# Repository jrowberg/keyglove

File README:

==What is Keyglove?

The Keyglove is an [http://arduino.cc Arduino]-powered glove that uses touch combinations to generate keyboard and mouse control codes. Once learned, the glove can easily be used without looking, making it perfect for embedded/wearable environments. The glove is thin and light, built to allow other activities (such as writing or driving) without being in the way.

==Keyglove Design

Because the glove design allows for multi-sensor combinations, the keyglove provides exponentially more possibilities than many other glove-based input devices (prototypes or commercial products). 34 strategically placed contact sensors and smart controller software make it possible to implement the entire English alphabet using simple one-to-one sensor contacts. When you include multi-sensor contacts, there are many hundreds of ergonomically usable combinations.

==Development Status

As of October 2010, the glove is currently in the prototype stage with no fully working unit, but I've done a lot of development and testing on it. At the moment, I'm only waiting on a little more hardware to arrive in the mail before I should be able to complete a working model. The source code is logically sound and works as much as possible without the remaining hardware to test it.

For up-to-date development news, check out the [http://keyglove.net/news News] page ([http://keyglove.net/feed RSS here]) or follow the project on Twitter at [http://twitter.com/keyglove @keyglove].

For technical information, please visit the [http://keyglove.net/hardware Hardware] and [http://keyglove.net/software Software] pages. Once the prototype is working, I will add step-by-step instructions to the [http://keyglove.net/build Build Your Own] page (which is currently devoid of any decent content except a [http://keyglove.net/build rather entertaining photo]).

You may also be interested in a [http://keyglove.net/similar list of similar devices] I've come across on the internet recently, either to satisfy your curiosity, or out of a need for inspiration, or possibly to look for a product that might be more suited to your needs.

And, of course, you can always [http://keyglove.net/contact contact me] with any questions, comments, ideas, etc.

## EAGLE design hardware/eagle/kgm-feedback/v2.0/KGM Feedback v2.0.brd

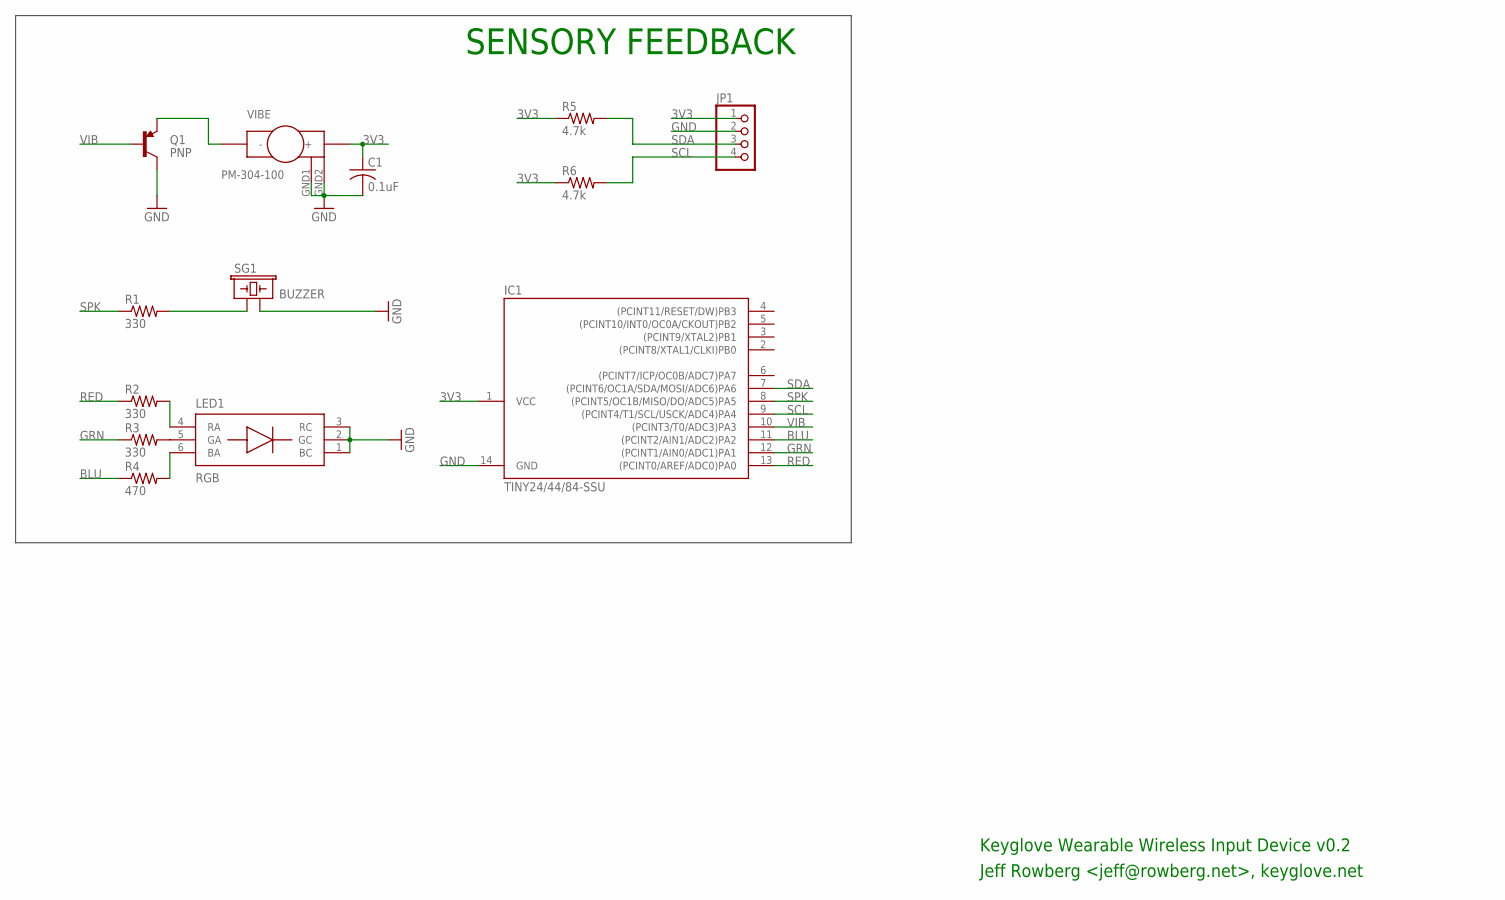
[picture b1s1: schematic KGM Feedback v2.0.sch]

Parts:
C1: 0.1uF; C0603
IC1: TINY24/44/84-SSU; SOIC14
JP1: PINHD-1X4; 1X04
LED1: RGB; PLCC-6
Q1: PNP; SOT23-3
R1, R2, R3: 330; R0603
R4: 470; R0603
R5, R6: 4.7k; R0603
SG1: BUZZER; BUZZER-CMT1102
VIBE: PM-304-100

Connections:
3V3: C1.1, IC1.1 (VCC), JP1.1, R5.1, R6.1, VIBE.+
BLU: IC1.11 ((PCINT2/AIN1/ADC2)PA2), R4.1
GND: C1.2, IC1.14 (GND), JP1.2, LED1.1 (BC), LED1.2 (GC), LED1.3 (RC), Q1.3 (C), SG1.2, VIBE.GND1 (GND), VIBE.GND2 (GND)
GRN: IC1.12 ((PCINT1/AIN0/ADC1)PA1), R3.1
unnamed: R1.2, SG1.1
unnamed: LED1.5 (GA), R3.2
unnamed: LED1.4 (RA), R2.2
unnamed: LED1.6 (BA), R4.2
unnamed: Q1.2 (E), VIBE.-
RED: IC1.13 ((PCINT0/AREF/ADC0)PA0), R2.1
SCL: IC1.9 ((PCINT4/T1/SCL/USCK/ADC4)PA4), JP1.4, R6.2
SDA: IC1.7 ((PCINT6/OC1A/SDA/MOSI/ADC6)PA6), JP1.3, R5.2
SPK: IC1.8 ((PCINT5/OC1B/MISO/DO/ADC5)PA5), R1.1
VIB: IC1.10 ((PCINT3/T0/ADC3)PA3), Q1.1 (B)

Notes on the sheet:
SENSORY FEEDBACK
Keyglove Wearable Wireless Input Device v0.2
Jeff Rowberg <jeff@rowberg.net>, keyglove.net

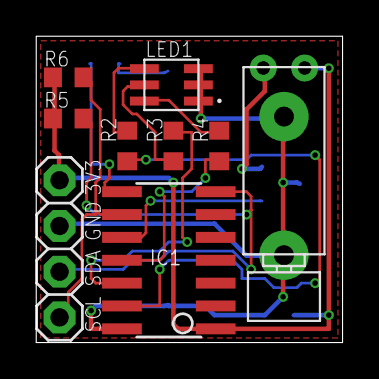
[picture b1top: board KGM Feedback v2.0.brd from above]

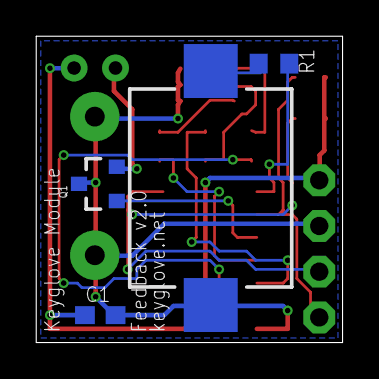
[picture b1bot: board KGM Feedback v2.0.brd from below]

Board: 2 copper layers, 17.0 x 17.0 mm, 13 parts (4 on the bottom side), 14 nets.

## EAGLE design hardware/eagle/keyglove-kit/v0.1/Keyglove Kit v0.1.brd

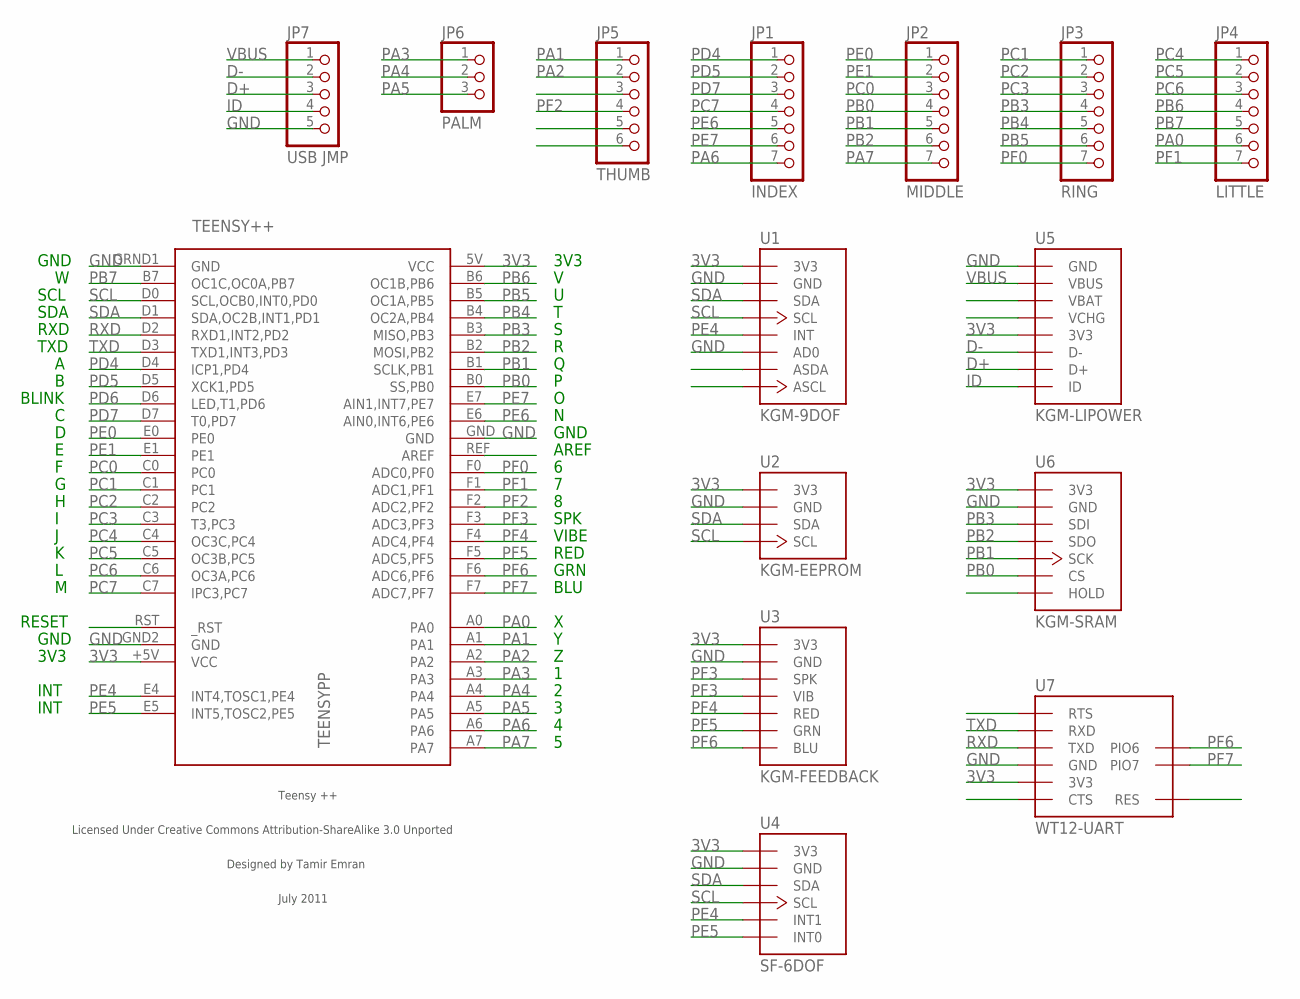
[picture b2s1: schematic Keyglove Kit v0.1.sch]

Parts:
JP1: INDEX; 1X07
JP2: MIDDLE; 1X07
JP3: RING; 1X07
JP4: LITTLE; 1X07
JP5: THUMB; 1X06
JP6: PALM; 1X03
JP7: USB JMP; 1X05
TEENSY++: TEENSYPP
U1: KGM-9DOF
U2: KGM-EEPROM
U3: KGM-FEEDBACK
U4: SF-6DOF
U5: KGM-LIPOWER
U6: KGM-SRAM
U7: WT12-UART

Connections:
3V3: TEENSY++.5V (VCC), TEENSY++.+5V (VCC), U1.3V3, U2.3V3, U3.3V3, U4.3V3, U5.3V3, U6.3V3, U7.3V3
D+: JP7.3, U5.D+
D-: JP7.2, U5.D-
GND: JP7.5, TEENSY++.GND, TEENSY++.GND2 (GND), TEENSY++.GRND1 (GND), U1.AD0, U1.GND, U2.GND, U3.GND, U4.GND, U5.GND, U6.GND, U7.GND
ID: JP7.4, U5.ID
PA0: JP4.6, TEENSY++.A0
PA1: JP5.1, TEENSY++.A1
PA2: JP5.2, TEENSY++.A2
PA3: JP6.1, TEENSY++.A3
PA4: JP6.2, TEENSY++.A4
PA5: JP6.3, TEENSY++.A5
PA6: JP1.7, TEENSY++.A6
PA7: JP2.7, TEENSY++.A7
PB0: JP2.4, TEENSY++.B0 (SS,PB0), U6.CS
PB1: JP2.5, TEENSY++.B1 (SCLK,PB1), U6.SCK
PB2: JP2.6, TEENSY++.B2 (MOSI,PB2), U6.SDO
PB3: JP3.4, TEENSY++.B3 (MISO,PB3), U6.SDI
PB4: JP3.5, TEENSY++.B4 (OC2A,PB4)
PB5: JP3.6, TEENSY++.B5 (OC1A,PB5)
PB6: JP4.4, TEENSY++.B6 (OC1B,PB6)
PB7: JP4.5, TEENSY++.B7 (OC1C,OC0A,PB7)
PC0: JP2.3, TEENSY++.C0
PC1: JP3.1, TEENSY++.C1
PC2: JP3.2, TEENSY++.C2
PC3: JP3.3, TEENSY++.C3 (T3,PC3)
PC4: JP4.1, TEENSY++.C4 (OC3C,PC4)
PC5: JP4.2, TEENSY++.C5 (OC3B,PC5)
PC6: JP4.3, TEENSY++.C6 (OC3A,PC6)
PC7: JP1.4, TEENSY++.C7 (IPC3,PC7)
PD4: JP1.1, TEENSY++.D4 (ICP1,PD4)
PD5: JP1.2, TEENSY++.D5 (XCK1,PD5)
PD6: TEENSY++.D6 (LED,T1,PD6)
PD7: JP1.3, TEENSY++.D7 (T0,PD7)
PE0: JP2.1, TEENSY++.E0
PE1: JP2.2, TEENSY++.E1
PE4: TEENSY++.E4 (INT4,TOSC1,PE4), U1.INT, U4.INT1
PE5: TEENSY++.E5 (INT5,TOSC2,PE5), U4.INT0
PE6: JP1.5, TEENSY++.E6 (AIN0,INT6,PE6)
PE7: JP1.6, TEENSY++.E7 (AIN1,INT7,PE7)
PF0: JP3.7, TEENSY++.F0 (ADC0,PF0)
PF1: JP4.7, TEENSY++.F1 (ADC1,PF1)
PF2: JP5.4, TEENSY++.F2 (ADC2,PF2)
PF3: TEENSY++.F3 (ADC3,PF3), U3.SPK, U3.VIB
PF4: TEENSY++.F4 (ADC4,PF4), U3.RED
PF5: TEENSY++.F5 (ADC5,PF5), U3.GRN
PF6: TEENSY++.F6 (ADC6,PF6), U3.BLUE (BLU), U7.PIO6
PF7: TEENSY++.F7 (ADC7,PF7), U7.PIO7
RXD: TEENSY++.D2 (RXD1,INT2,PD2), U7.TXD
SCL: TEENSY++.D0 (SCL,OCB0,INT0,PD0), U1.SCL, U2.SCL, U4.SCL
SDA: TEENSY++.D1 (SDA,OC2B,INT1,PD1), U1.SDA, U2.SDA, U4.SDA
TXD: TEENSY++.D3 (TXD1,INT3,PD3), U7.RXD
VBUS: JP7.1, U5.VBUS

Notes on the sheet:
SCL
SDA
RXD
TXD
BLINK
RESET
GND
3V3
INT
AREF
SPK
VIBE
RED
GRN
BLU

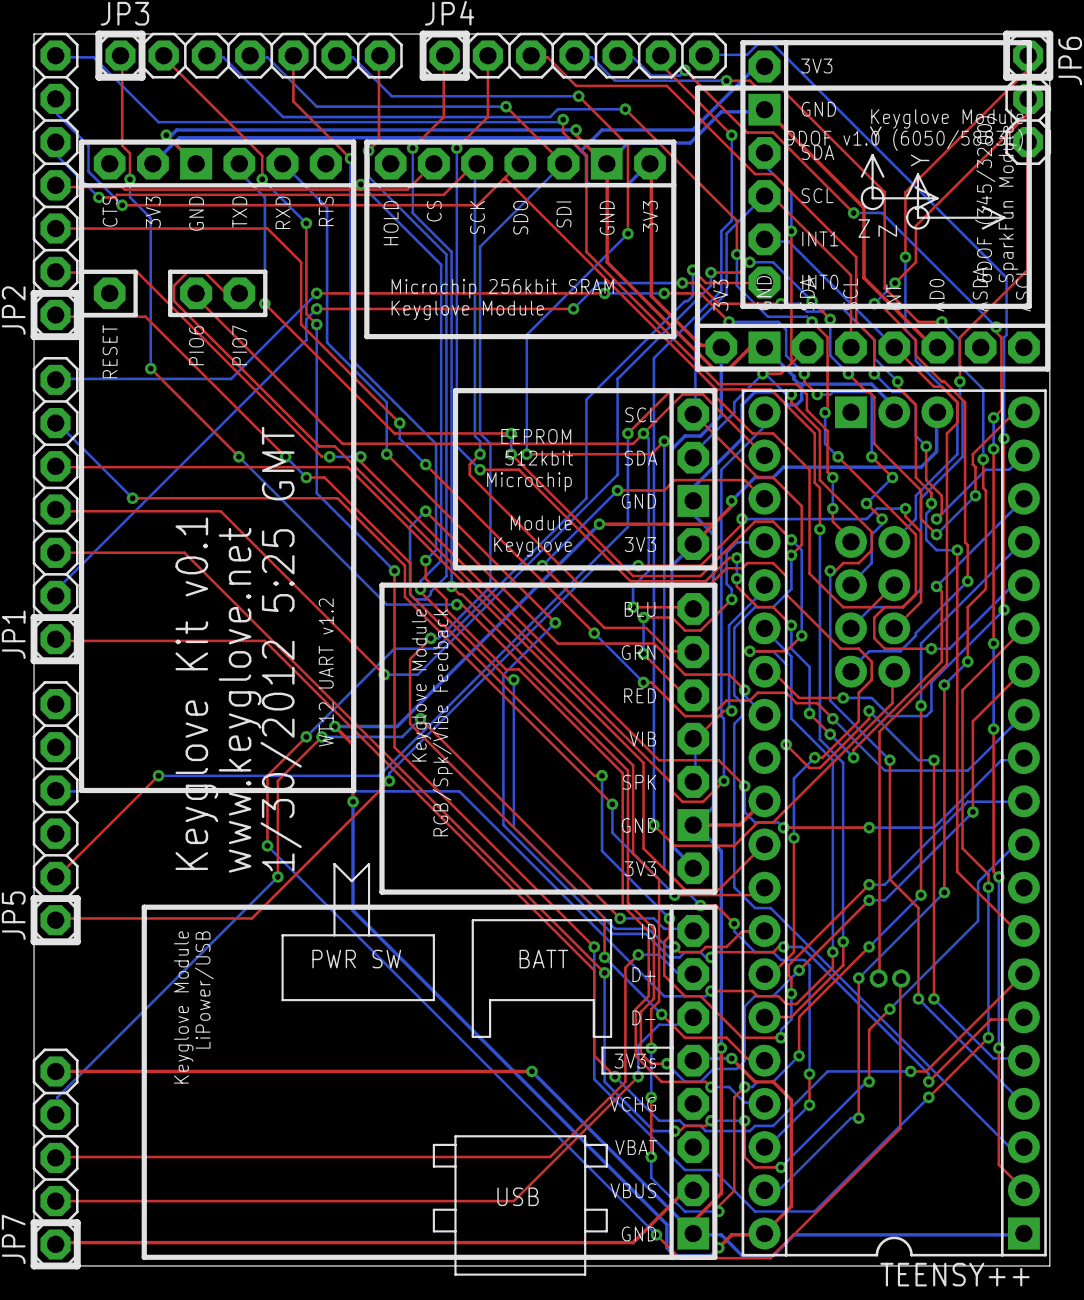
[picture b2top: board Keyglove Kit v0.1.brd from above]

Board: 2 copper layers, 59.7 x 72.4 mm, 15 parts (0 on the bottom side), 51 nets.

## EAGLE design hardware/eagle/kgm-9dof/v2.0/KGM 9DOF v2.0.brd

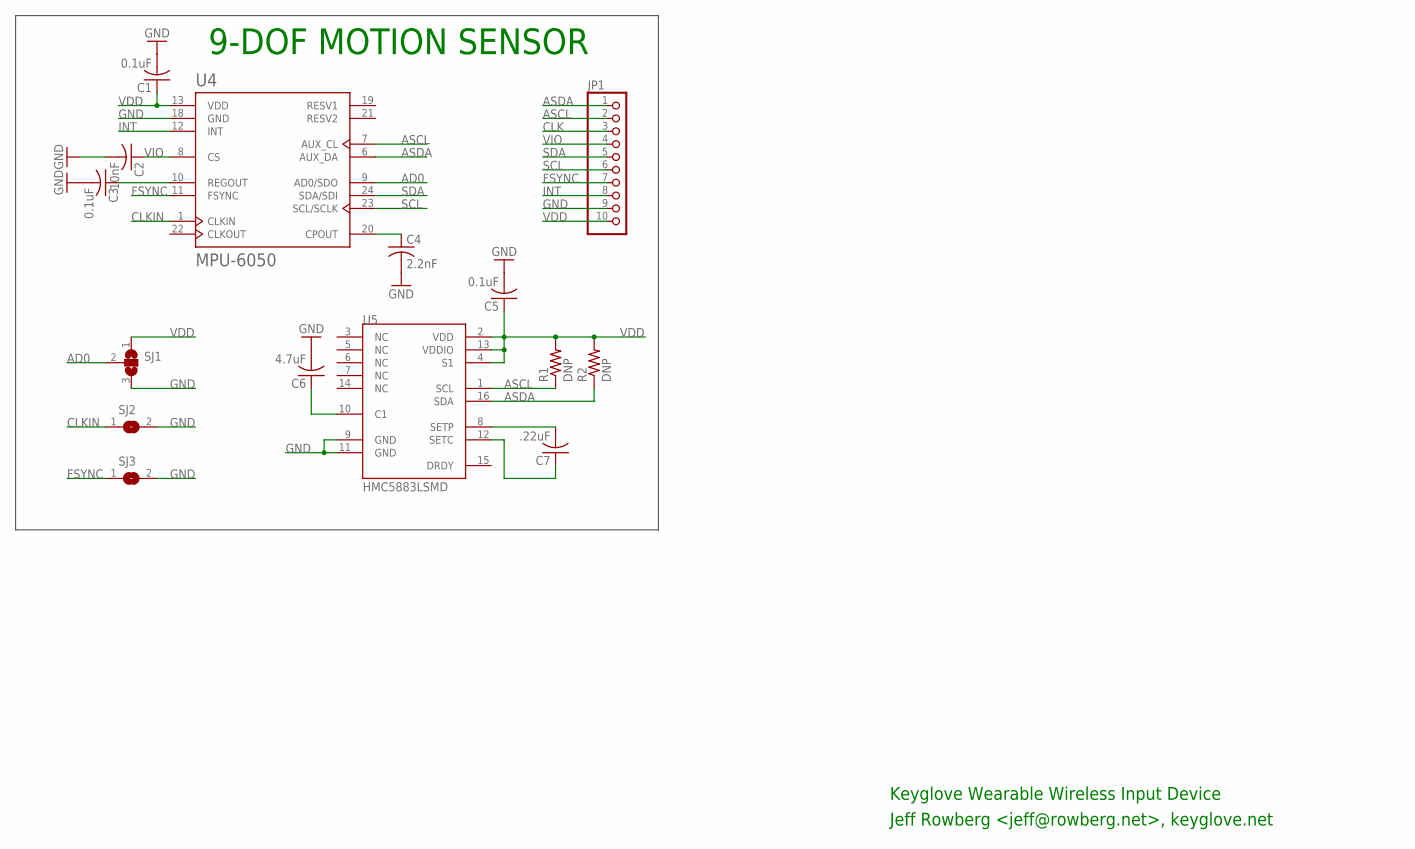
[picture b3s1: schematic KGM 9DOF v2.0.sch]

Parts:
C1, C3, C5: 0.1uF; C0603
C2: 10nF; C0603
C4: 2.2nF; C0603
C6: 4.7uF; C0603
C7: .22uF; C0603
JP1: PINHD-1X10; 1X10
R1, R2: DNP; R0603
SJ1: SJ2W; SJ_2
SJ2, SJ3: SJ
U4: MPU-6050; QFN24MPU
U5: HMC5883LSMD; 16LPCC

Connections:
AD0: SJ1.2, U4.9 (AD0/SDO)
ASCL: JP1.2, R1.1, U4.7 (AUX_CL), U5.1 (SCL)
ASDA: JP1.1, R2.1, U4.6 (AUX_DA), U5.16 (SDA)
CLK: JP1.3
CLKIN: SJ2.1, U4.1 (CLKIN)
FSYNC: JP1.7, SJ3.1, U4.11 (FSYNC)
GND: C1.2, C2.2, C3.2, C4.2, C5.2, C6.2, JP1.9, SJ1.3, SJ2.2, SJ3.2, U4.18 (GND), U5.9 (GND), U5.11 (GND)
INT: JP1.8, U4.12 (INT)
unnamed: C6.1, U5.10 (C1)
unnamed: C7.2, U5.8 (SETP)
unnamed: C7.1, U5.12 (SETC)
unnamed: C4.1, U4.20 (CPOUT)
unnamed: C3.1, U4.10 (REGOUT)
SCL: JP1.6, U4.23 (SCL/SCLK)
SDA: JP1.5, U4.24 (SDA/SDI)
VDD: C1.1, C5.1, JP1.10, R1.2, R2.2, SJ1.1, U4.13 (VDD), U5.2 (VDD), U5.4 (S1), U5.13 (VDDIO)
VIO: C2.1, JP1.4, U4.8 (CS)

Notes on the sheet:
9-DOF MOTION SENSOR
Keyglove Wearable Wireless Input Device
Jeff Rowberg <jeff@rowberg.net>, keyglove.net

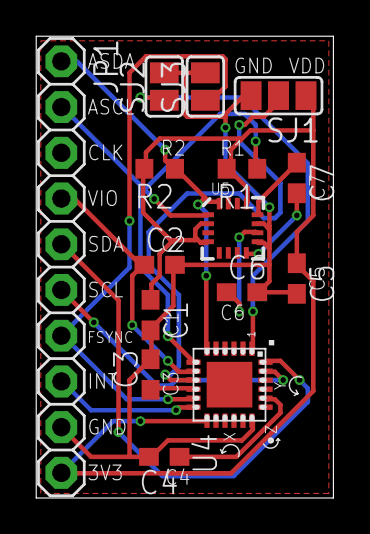
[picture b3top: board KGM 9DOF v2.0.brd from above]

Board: 2 copper layers, 16.5 x 25.7 mm, 15 parts (0 on the bottom side), 16 nets.

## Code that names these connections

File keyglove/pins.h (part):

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
#if (defined(__AVR_ATmega168__) || defined(__AVR_ATmega328__))
     // 32-pin ATMegaxxx MCUs
     #define SS   PB0
     #define SCLK PB1
     #define MOSI PB2
     #define MISO PB3
     #define SCL  PD0
     #define SDA  PD1
#endif

#if (defined(__AVR_AT90USB162__))
     // 32-pin AT90USB MCUs
     #define SS   PB0
     #define SCLK PB1
     #define MOSI PB2
     #define MISO PB3
     #define SCL  PD0
     #define SDA  PD1
#endif

#if (defined(__AVR_ATmega16U4__) || defined(__AVR_ATmega32U4__))
     // 44-pin ATMEGAxxUx MCUs
     #define SS   PB0
     #define SCLK PB1
     #define MOSI PB2
     #define MISO PB3
     #define SCL  PD0
     #define SDA  PD1
#endif

#if (defined(__AVR_ATmega1280__) || defined(__AVR_ATmega2560__))
     // 100-pin ATMegaxxx0 MCUs
     #define SS   PB0
     #define SCLK PB1
     #define MOSI PB2
     #define MISO PB3
     #define SCL  PD0
     #define SDA  PD1
#endif

#if (defined(__AVR_AT90USB1287__) || defined(__AVR_AT90USB647__) || \
     defined(__AVR_AT90USB1286__) || defined(__AVR_AT90USB646__) || \
     defined(__AVR_ATmega32U6__))
     // 64-pin AT90USB MCUs
     #define SS   PB0
     #define SCLK PB1
     #define MOSI PB2
     #define MISO PB3
     #define SCL  PD0
     #define SDA  PD1
#endif


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    and so on. Start with pin 26 (B6)
    */

    #define KSP_Y   26  // PB6
    #define KSP_Z   25  // PB5
    #define KSP_AA  24  // PB4
    #define KSP_8   23  // PB3
    #define KSP_9   22  // PB2
    #define KSP_0   21  // PB1

    #define KSP_A   20  // PB0
    #define KSP_B   38  // PF0
    #define KSP_C   39  // PF1
    #define KSP_M   40  // PF2
    #define KSP_N   41  // PF3
    #define KSP_O   42  // PF4
    #define KSP_4   43  // PF5

    #define KSP_D   44  // PF6
    #define KSP_E   45  // PF7
    #define KSP_F   31  // PA3
    #define KSP_P   30  // PA2
    #define KSP_Q   29  // PA1
    #define KSP_R   28  // PA0
    #define KSP_5   32  // PA4

    #define KSP_G   33  // PA5
    #define KSP_H   34  // PA6
    #define KSP_I   35  // PA7
    #define KSP_S   17  // PC7
    #define KSP_T   16  // PC6
    #define KSP_U   15  // PC5
    #define KSP_6   14  // PC4

    #define KSP_J   13  // PC3
    #define KSP_K   12  // PC2
    #define KSP_L   11  // PC1
    #define KSP_V   10  // PC0
    #define KSP_W   9   // PE1
    #define KSP_X   8   // PE0
    #define KSP_7   7   // PD7

    #define KSP_1   5   // PD5
    #define KSP_2   4   // PD4
    #define KSP_3   27  // PB7

    #define KG_INTERRUPT_PIN_ACCEL  36  // PE4 (internal/tiny, right)
    #define KG_INTERRUPT_NUM_ACCEL  4   // Teensy++ interrupt #4
    // KKYX-9CL3X2-ZXZ2

    #define KG_INTERRUPT_PIN_GYRO   37  // PE5 (internal/tiny, left)
    #define KG_INTERRUPT_NUM_GYRO   5   // Teensy++ interrupt #5

    // FUSION and ACCEL are never both used at the same time
    #define KG_INTERRUPT_PIN_FUSION 36  // PE4 (internal/tiny, right)
    #define KG_INTERRUPT_NUM_FUSION 4   // Teensy++ interrupt #4

    #define KG_PIN_BLINK            6   // PD6

    #define KG_PIN_BT_LINK              19  // PE7
    #define KG_INTERRUPT_NUM_BT_LINK    7   // Teensy++ interrupt #7
    #define KG_PIN_BT_DTR               18  // PE6

    // ITEMS BELOW THIS CANNOT BE USED SIMULTANEOUSLY WITH ALL ABOVE FEATURES

    // direct I/O feedback pins (kills 3 thumb sensors and Bluetooth mode control)
    #define KG_PIN_PIEZO        19  // PE7
    #define KG_PIN_VIBRATE      18  // PE6
    #define KG_PIN_RGB_RED      21  // PB1
    #define KG_PIN_RGB_GREEN    22  // PB2
    #define KG_PIN_RGB_BLUE     24  // PB4

    // PS/2 clock/data pins for keyboard (kills Bluetooth mode control, direct I/O piezo/vibe)
    #define KG_PIN_KB_CLOCK     19  // PE7
    #define KG_PIN_KB_DATA      18  // PE6

    // PS/2 clock/data pins for mouse (kills Bluetooth UART connection)
    #define KG_PIN_MOUSE_CLOCK  3   // PD3
    #define KG_PIN_MOUSE_DATA   2   // PD2
#endif /* KG_BOARD == KG_BOARD_TEENSYPP2 */

#define KG_TOTAL_SENSORS 37
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
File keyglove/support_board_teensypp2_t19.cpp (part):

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
                         __|||||__
                    GND |   USB   | VCC
        1        PB7 27 |         | 26 PB6        Y
            SCL  PD0  0 |         | 25 PB5        8
            SDA  PD1  1 |         | 24 PB4    SPK
            RXD  PD2  2 |         | 23 PB3    VIB
            TXD  PD3  3 |         | 22 PB2    CS2 (STAT2)
            RTS  PD4  4 |  37.36  | 21 PB1    CS1 (STAT1)
        7        PD5  5 |         | 20 PB0    CS0 (/PG)
            LED  PD6  6 |         | 19 PE7    CTS (INT7)
        L        PD7  7 |         | 18 PE6    MPU (INT6)
        K        PE0  8 |         | GND
        J        PE1  9 |         | AREF
        6        PC0 10 |         | 38 PF0    BAT (VBDIV)
        I        PC1 11 | 32 . 28 | 39 PF1        A
        H        PC2 12 | 33 . 29 | 40 PF2        B
        G        PC3 13 | 34 . 30 | 41 PF3        C
            RED  PC4 14 | 35 . 31 | 42 PF4        4
            GRN  PC5 15 |         | 43 PF5        D
            BLU  PC6 16 |         | 44 PF6        E
        5        PC7 17 |_________| 45 PF7        F

                      36=INT4, 37=INT5

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- We use INT7 (19) for CTS interrupts (WT12 RTS), leaving 40 usable pins
- We use INT6 (18) for accel/gyro interrupt, leaving 39 usable pins
- We use LED (6) for BLINK feedback, leaving 38 usable pins.
- We use SPK (24) for piezo buzzer feedback, leaving 37 usable pins.
- We use VIB (23) for vibration motor feedback, leaving 36 usable pins.
- We use REG/GRN/BLU (14/15/16) for RGB feedback, leaving 33 usable pins.
- We use CS1/CS2/CS3 (22/21/20) for charge state indicators, leaving 30 usable pins.
- We use BAT (38) for battery level measurement (ADC), leaving 29 usable pins.
- ...and we have a total of 19 sensors. There's some wiggle room here (10 extra pins).

Pin Change interrupts (not currently used, could help with sleep modes):

- 1,   27, PB7
- Y,   26, PB6
- 8,   25, PB5
- SPK, 24, PB4
- VIB, 23, PB3
- CS1, 22, PB2
- CS2, 21, PB1
- CS3, 20, PB0
- 7,   5,  PD5
- RTS, 4,  PD4

For the sake of the Keyglove Kit board, the sensor pin connections should be arranged
in a clockwise manner as Thumb, Index, Middle, Ring, Little, with each individual
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
    // set up pin change interrupts on relevant Port B pins
    PCICR = 0x01;   // PCICR: PCIE0=1 (enable pin change interrupts)
    PCMSK0 = 0x07;  // PCMSK0: PCINT0/1/2=1 (enable PB0/PB1/PB2 pins)

    /*
                         __|||||__
                    GND |   USB   | VCC
        1        PB7 27 |         | 26 PB6        Y
            SCL  PD0  0 |         | 25 PB5        8
            SDA  PD1  1 |         | 24 PB4    SPK
            RXD  PD2  2 |         | 23 PB3    VIB
            TXD  PD3  3 |         | 22 PB2    CS2 (STAT2)
            RTS  PD4  4 |  37.36  | 21 PB1    CS1 (STAT1)
        7        PD5  5 |         | 20 PB0    CS0 (/PG)
            LED  PD6  6 |         | 19 PE7    CTS (INT7)
        L        PD7  7 |         | 18 PE6    MPU (INT6)
        K        PE0  8 |         | GND
        J        PE1  9 |         | AREF
        6        PC0 10 |         | 38 PF0    BAT (VBDIV)
        I        PC1 11 | 32 . 28 | 39 PF1        A
        H        PC2 12 | 33 . 29 | 40 PF2        B
        G        PC3 13 | 34 . 30 | 41 PF3        C
            RED  PC4 14 | 35 . 31 | 42 PF4        4
            GRN  PC5 15 |         | 43 PF5        D
            BLU  PC6 16 |         | 44 PF6        E
        5        PC7 17 |_________| 45 PF7        F
    */

    // setup touch/battery sensors and make sure we enable internal pullup resistors EXCEPT on PF0 (BAT)
    DDRB  &=  (0x18);   // 7,6,5, , ,2,1,0
    PORTB |= ~(0x18);
    DDRC  &=  (0x70);   // 7, , , ,3,2,1,0
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
    /*
    Relevant pin change interrupts for touch sensors:
    - 1, 27, PB7 (palm)
    - Y, 26, PB6 (thumbtip)
    - 8, 25, PB5 (thumbnail)
    */

    #if KG_HOSTIF & KG_HOSTIF_USB_SERIAL
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    /*
                         __|||||__
                    GND |   USB   | VCC
        1        PB7 27 |         | 26 PB6        Y
            SCL  PD0  0 |         | 25 PB5        8
            SDA  PD1  1 |         | 24 PB4    SPK
            RXD  PD2  2 |         | 23 PB3    VIB
            TXD  PD3  3 |         | 22 PB2    CS2 (STAT2)
            RTS  PD4  4 |  37.36  | 21 PB1    CS1 (STAT1)
        7        PD5  5 |         | 20 PB0    CS0 (/PG)
            LED  PD6  6 |         | 19 PE7    CTS (INT7)
        L        PD7  7 |         | 18 PE6    MPU (INT6)
        K        PE0  8 |         | GND
        J        PE1  9 |         | AREF
        6        PC0 10 |         | 38 PF0    BAT (VBDIV)
        I        PC1 11 | 32 . 28 | 39 PF1        A
        H        PC2 12 | 33 . 29 | 40 PF2        B
        G        PC3 13 | 34 . 30 | 41 PF3        C
            RED  PC4 14 | 35 . 31 | 42 PF4        4
            GRN  PC5 15 |         | 43 PF5        D
            BLU  PC6 16 |         | 44 PF6        E
        5        PC7 17 |_________| 45 PF7        F
    */

    // check on Y combinations (PB6)
    SET(DDRB, 6);       // set to OUTPUT
    CLR(PORTB, 6);      // set to LOW
    delayMicroseconds(3); // give the poor receiving pins a chance to change state
    _pinb = PINB; _pinc = PINC; _pind = PIND; _pine = PINE; _pinf = PINF;
    CLR(DDRB, 6);       // set to INPUT
    SET(PORTB, 6);      // pull HIGH
    if (!(_pinf & (1 << 1))) touches[0] |= 0x01;    // A (PF1)
    if (!(_pinf & (1 << 2))) touches[0] |= 0x02;    // B (PF2)
    if (!(_pinf & (1 << 3))) touches[0] |= 0x04;    // C (PF3)
    if (!(_pinf & (1 << 5))) touches[0] |= 0x08;    // D (PF5)
    if (!(_pinf & (1 << 6))) touches[0] |= 0x10;    // E (PF6)
    if (!(_pinf & (1 << 7))) touches[0] |= 0x20;    // F (PF7)
    if (!(_pinc & (1 << 3))) touches[0] |= 0x40;    // G (PC3)
    if (!(_pinc & (1 << 2))) touches[0] |= 0x80;    // H (PC2)
    if (!(_pinc & (1 << 1))) touches[1] |= 0x01;    // I (PC1)
    if (!(_pine & (1 << 1))) touches[1] |= 0x02;    // J (PE1)
    if (!(_pine & (1 << 0))) touches[1] |= 0x04;    // K (PE0)
    if (!(_pind & (1 << 7))) touches[1] |= 0x08;    // L (PD7)
    if (!(_pinf & (1 << 4))) touches[1] |= 0x10;    // 4 (PF4)
    if (!(_pinc & (1 << 7))) touches[1] |= 0x20;    // 5 (PC7)
    if (!(_pinc & (1 << 0))) touches[1] |= 0x40;    // 6 (PC0)
    if (!(_pind & (1 << 5))) touches[1] |= 0x80;    // 7 (PD5)
    if (!(_pinb & (1 << 7))) touches[2] |= 0x01;    // 1 (PB7)

    // check on 1 combinations (PB7)
    SET(DDRB, 7);       // set to OUTPUT
    CLR(PORTB, 7);      // set to LOW
    delayMicroseconds(3); // give the poor receiving pins a chance to change state
    _pinc = PINC; _pine = PINE; _pinf = PINF;
    CLR(DDRB, 7);       // set to INPUT
    SET(PORTB, 7);      // pull HIGH
    if (!(_pinf & (1 << 1))) touches[2] |= 0x02;    // A (PF1)
    if (!(_pinf & (1 << 5))) touches[2] |= 0x04;    // D (PF5)
    if (!(_pinc & (1 << 3))) touches[2] |= 0x08;    // G (PC3)
    if (!(_pine & (1 << 1))) touches[2] |= 0x10;    // J (PE1)

    // check on 8 combinations (PB5)
    SET(DDRB, 5);       // set to OUTPUT
    CLR(PORTB, 5);      // set to LOW
    delayMicroseconds(3); // give the poor receiving pins a chance to change state
    _pinc = PINC; _pine = PINE; _pinf = PINF;
    CLR(DDRB, 5);       // set to INPUT
    SET(PORTB, 5);      // pull HIGH
    if (!(_pinf & (1 << 1))) touches[2] |= 0x20;    // A (PF1)
    if (!(_pinf & (1 << 5))) touches[2] |= 0x40;    // D (PF5)
    if (!(_pinc & (1 << 3))) touches[2] |= 0x80;    // G (PC3)
    if (!(_pine & (1 << 1))) touches[3] |= 0x01;    // J (PE1)
}

#endif
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
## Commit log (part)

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2010-10-07 Initial existing Keyglove code import
2010-10-08 Updated main loop with correct test code for PS/2 keyboard library. It outputs a 'k' keypress code roughly once per second--still obviously in the testing stage. The keyboard library works though! I 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
2010-10-13 Updated sensor definitions with new 34-sensor arrangement. Not every possible combination is done, but more than enough for a good touchset. I will probably leave the rest undone until I get my proto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
2010-10-17 New code that is slightly faster, shows correct base pin combination status array for debugging, and has correct pin array references. Working great so far!
2010-10-27 Updated code to include simultaneous keyboard/mouse PS2 devices (technically these are unique, NOT all in one cable!). I can hardly wait for USB on the Teensy.
2010-11-01 Keyglove Data Visualization Test Processing sketch initial commit
2010-11-01 Updates to integrate with current version of Processing sketch code
2010-11-14 Updated to reflect more touch functionality and the beginnings of a full touchset.
2010-11-14 Updated to show sensor touches more accurately.
2010-11-19 Updated order of currently entered touch combinations to reflect likely touches vs. unlikely (avoids mistakes due to unintended double touches)
2011-01-23 Updated to support changed accelerometer serial debug code (includes linear and angular velocity values).
2011-02-07 Updated code to include haptic feedback (vibration), audio feedback (piezo buzzer), other small changes.
2011-02-07 Removed locally, now removing from repository
2011-04-24 Not necessary in current code.
2011-05-04 Commit to make sure SVN is fresh before importing to Github
2011-05-30 Small updates to accel/gyro processing code
2011-05-30 Fix case of include filename
2011-05-30 Add rough code to use a Logitech RX400 board and reciever to get keyboard and mouse events back to the computer
2011-05-30 Wrap all the Keyboard and Mouse calls in ENABLE_USB defines
2011-05-30 Add missing pins for Arduino board
2011-05-30 define the Uart using already defined variables on Arduino
2011-05-30 Rename ITG files to match upstream
2011-05-30 Use constants for readability
2011-05-30 Fix mouse up for middle and right buttons
2011-05-30 Add a partial beep() implementation
2011-05-30 Allow modeCheck to be used to check multiple levels in the mode stack.Fix toggle mode off by one.Pass the mode stack position to check_sensor_* functions
2011-05-30 Commit the touchset that I'm using. Has four modes: default (a-z), number, symbol, function. Define all keys on a 101 keyboard except: cursor keys, home, end, pgup, pgdown, capslock Modifier keys (ct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
2011-05-30 Fix modifier and mode toggle. Mouse off by default
2011-05-30 Do proper toggle but for keyboard too
2011-05-30 Change the precedence on a couple of combinations that I accidently hit a second contact at the same time
2011-05-30 Verified merges from mikeNZ, updated README
2011-06-11 Updates to tilt calculation code, added accel/gyro rotation settings, disabled vibration motor temporarily. New files include 3D axis template for Google SketchUp and PHP smart touchset generation sc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
2011-06-11 Updated PHP touchset scripts with slight modifications
2011-07-01 Fixed USB descriptor in LUFA version so that all devices enumerate correctly
2011-07-05 New changes to LUFA test code for updated Serial and HID structure
2011-07-05 Fixed generic HID endpoint address constants to make virtual serial IO work
2011-07-07 Created LUFA demo code for similar projects
2011-07-09 Integrated Wiring with LUFA, modified Keyglove LUFA code to incorporate existing Arduino code and compile with limited functionality so far.
2011-07-09 Added Wiring code to repository
2011-07-15 Fixed JTAG pins to be used as I/O, updated license in new source files
2011-07-21 Massive code structure changes, constant definition fixes, hardware abstraction, debug code changes, C99 variable standards
2011-07-22 Update files included in repository
2011-07-22 Remove misnamed files from repository
2011-07-22 Final clean-up of missing files, mis-named files, and general repository adjustments
2011-09-26 Update new files, convert to Arduino 1.0 compatibility
2011-09-26 Remove old files, no longer necessary
2011-09-26 Added schematics and PCBs for the current batch of independent Keyglove modules
2011-09-29 Add 6DOF and 9DOF schematic/PCB image files for quick reference
2011-09-30 Add new files from LUFA framework 111009
2011-10-01 Update LUFA to 111009, I2Cdev class to include new NBWire implementation to remove Arduino Wire dependency
2011-10-04 Add missing LUFA framework files to repository
2011-10-04 New Processing sketch for motion development and testing
2011-10-26 Updated LUFA library source code to new stable release
2011-10-26 Major updates for interrupt-driven behavior, motion processing (which is still a bit buggy), and serial communication protocol
2011-10-26 Add new setup_motion header file
2011-10-31 Move raw IMU motion functionality to its own header file
2011-10-31 Update motion control, fix interrupt problem, set I2C implemention back to Arduino Wire for the time being, add more serial control commands.
2011-11-01 Fix scaling of IMU filter gyro update arguments
2011-12-14 Add the new math helper code and generic iWRAP setup header
2011-12-14 Update for new Bluetooth support, motion control, and re-enabled touch detection
2012-01-30 Update touchset helpers to fix piezo/vibrate feedback
2012-02-15 Added partial ATTiny44 feedback module control code
2012-02-15 Fix a bug in the RGB level setting in regular blink mode
2012-02-15 Moved default registers to PROGMEM, fixed per-byte configuration application method and I2C control to fit in available RAM
2012-03-08 Added simple I2C slave test program for ATTiny44 MCU
2012-03-08 Update test program with a few docs
2012-03-08 Major improvements to main RGB driver code, fully functional except I2C
2012-03-09 Greatly simplified entire codebase, added I2C START callback, tested and completely working
2012-05-26 Add KG Kit v0.1-v0.4, KGM 9DOF v2.0, EEPROM v1.1, Feedback v2.0 and v2.1
2012-05-26 MPU-6050 raw support, new structural changes, serial protocol basics, I2C feedback support
2012-05-26 Renamed setup_motion_rawimu.h to setup_motion_rawimu_6dof.h
2012-06-01 Update all code to include latest changes (serial protocol and motion control primarily)
2012-06-04 Fixed minor timing bugs in feedback slave module code
2012-07-03 New files, MPU code, 400kHz I2C, serial protocol, and scaled gyro measurements for better mouse control
2012-07-04 Minor update to WT12 Prep sketch
2012-07-04 Adding instructive comments to WT12 Prep sketch
2012-07-07 Major structural code changes, host interface protocol development
2012-07-09 Raw HID output support, host interface protocol improvements
2013-09-02 Adding Keyglove-specific Eagle libraries in their current state
2013-09-08 Committing all latest changes (including early Arduino Due support) before restructuring code
2013-11-17 Adding Python KGLib code and serial/rawhid demo apps
2013-11-21 Bundled clean serial + HID transport into KGLib code, added send_and_return() method for easier response handling
2013-11-24 Fix MPU-6050 hand motion sensor interrupt functionality
2014-07-28 Massive update to integrate new KGAPI structure, complete Doxygen documentation, and working fundamental firmware implementation on Teensy++ 2.0 platform
2014-08-02 Fix kg_cmd_bluetooth_set_mode() to fail if interface is not ready, not just if it is not ready AND the new mode is different
2014-08-02 Update support_bluetooth2_iwrap.h date
2014-08-04 Updating Python KGLib implementation and console test script
2014-11-02 Add support for 19-pin configuration with Teensy++ 2.0
2014-11-02 Add kg_evt_system_battery_status event and support for scheduled soft timers
2014-11-02 Update example application.h code
2014-11-02 Bring protocol support definition files current
2014-11-02 Add correct fading pulse support to visual feedback routines
2014-11-02 Clean up MPU6050 hand motion sensor code for efficiency and proper API integration
2014-11-02 Surround relevant code blocks with modular config conditional statements
2014-11-02 Add explicit zero-checking and braces to kg_evt_* and packet sending calls for safety
2014-11-03 Add explicit zero assignments to function pointers, add name length back into "name" event
2014-11-03 Add pairing array boundary checking to autocall algorithm
2014-11-09 Restructure Arduino project into standard .cpp/.h form, update Doxygen comments
2014-11-09 Update all files with properly synced changes
2014-11-11 Fix whitespace because I am ridiculously picky
2014-11-13 Add separators to dynamic BT device name
2014-11-15 Set Bluetooth discoverable if in the right mode after deleting pairings
2014-11-15 Close links when removing pairings, fix infinite loop bug in bluetooth_get_connections
2014-11-18 Fix HID support includes when Serial+3xHID mode is selected in IDE
2014-11-18 Modify touch status checks to run constantly when touches are active to reduce latency
2014-11-21 Make BT links attempt to take MASTER role every time
2014-11-28 Update support .cpp./h file autogenerator and resulting files
2014-11-28 Rename some Bluetooth pairing/index method parameters
2014-11-30 Fix Bluetooth link closure event handler to remove mapped connection
2014-11-30 Change system_reset() command arg 'type' to 'mode' for cleaner Python code
2014-12-06 Remove old and irrelevant material to tidy up
2014-12-06 Add Doxygen documentation to repository
2014-12-06 Add KGAPI definition in JSON format
2014-12-06 Update main repository README file
2014-12-06 Fix Python KGLib code to use latest source file
2014-12-06 Remove PyUSB test for kernel driver attachment
2014-12-06 Add timeout handler for new Linux PyUSB test
2014-12-06 Remove debug output for PyUSB endpoint write tests
2014-12-06 Remove extra "Disconnected" message from console stub
2014-12-07 Remove unnecessary 0xFF bitmask from uint16_t value that is already < 256
2014-12-07 Add README link to main project page, embedded prototype image
2014-12-07 Fix unlikely exception in send_and_return() method
2014-12-07 Increase version number container size to uint16_t and add protocol version
2014-12-07 Update kglib.py with kg_evt_system_boot() changes
2014-12-07 Add API-based generator PHP script and template files
2014-12-07 Add early draft KGAPI Reference Guide HTML document
2014-12-07 Update "system" protocol support files with new version info in system_get_info()
2014-12-08 Fix system_get_info() command to include new version data
2014-12-08 Update KGAPI JSON definition, Python KGLib, and HTML API ref for new version info in system_get_info() command
2014-12-08 Add system_get_capabilites() command and system_capability() event to API definition
2014-12-08 Update API ref HTML to reflect new changes, add quick PDF version
2014-12-08 Add extra CSS page break rules to API ref HTML template
2014-12-08 Add capability API request declarations to Arduino and Python code
2014-12-08 Add skeletal implementation of system_get_capabilities() command
2014-12-08 Add version and update date in KGAPI JSON definition
2014-12-14 Remove unnecessary KG_FEEDBACKCONN macros
2014-12-14 Rename KGAPI interface direction/purpose macros
2014-12-14 Remove basically pointless DEBUG macros
2014-12-14 Move Bluetooth API class after system class instead of at end
2014-12-14 Move feedback API class after Bluetooth
2014-12-15 Basic capability reporting event structure for currently existing categories
2014-12-15 Change capability category value to uint8_t instead of uint16_t
2015-03-14 Fix bitwise logic error in battery status value assignment
2015-03-14 Change battery measurements to use MAX17048 instead of ADC input
2015-04-01 Fix typo in vibrate code referring to piezo hardware
2015-04-01 Add conditional macro around Bluetooth code in sample application
2015-04-01 Include specific feedback header files to avoid compile errors with certain config selections
2015-04-06 Add root .gitignore
2015-04-06 Fix compilation with Bluetooth and motion disabled

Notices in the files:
keyglove/pins.h:
Controller code is placed under the MIT license
Copyright (c) 2011 Jeff Rowberg
keyglove/support_board_teensypp2_t19.cpp:
Copyright (c) 2014 Jeff Rowberg
parts and their libraries:
sf-keyglovekit: Teensy++ board by PJRC. Eagle part designed by Tamir Emran, July 2011. Licensed under Create Commons Attribution-ShareAlike 3.0 Unported license (CC-BY-SA-3.0).
sf-keyglovekit: Licensed Under Creative Commons
